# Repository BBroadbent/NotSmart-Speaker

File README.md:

# NotSmart Speaker

> **All the beats. None of the privacy risks.**

**NotSmart Speaker** is a custom, open-hardware local-first audio receiver designed to bring high-fidelity multi-room streaming to your home without the bloat, telemetry, or invasive microphones of commercial "smart" speakers. 

Powered by an ESP32 micro-controller, a PCM5100A I2S DAC, and a TPA3118 Class-D amplifier, it connects directly over Wi-Fi via the **Sendspin** protocol (integrating seamlessly with Home Assistant, Music Assistant, and local media setups).

---

## Features

- **100% Local & Cloud-Free:** No voice tracking, no external server dependency, no telemetry, and zero microphones.
- **20V USB-PD Powered:** Runs off a standard 45W+ USB-C laptop power brick using an onboard CH224K USB Power Delivery trigger IC.
- **Hi-Fi I2S Digital Path:** Uses the PCM5100A DAC to convert digital I2S audio signals straight from the ESP32.
- **Punchy Class-D Output:** Drives a single 4Ω mono speaker with up to ~40W cleanly via a TPA3118 amplifier in PBTL mode.
- **Clean Power Tree:** Dedicated buck step-down and low-noise LDO stages to protect sensitive audio lines from power noise.
- **Open Hardware:** Custom PCB layout engineered specifically for small desktop/shelf speaker enclosures.

---

## Hardware Architecture

### **Core Components**
| Component | Function |
| :--- | :--- |
| **ESP32** | Main microcontroller running local audio client firmware |
| **PCM5100A** | Dedicated I2S stereo/mono DAC |
| **TPA3118** | High-efficiency Class-D mono (PBTL) audio power amplifier |
| **CH224K** | Hardware USB-PD sink controller (Requests 20V profile) |
| **4Ω Mono Speaker** | Custom cabinet integration |

### **Power Architecture**

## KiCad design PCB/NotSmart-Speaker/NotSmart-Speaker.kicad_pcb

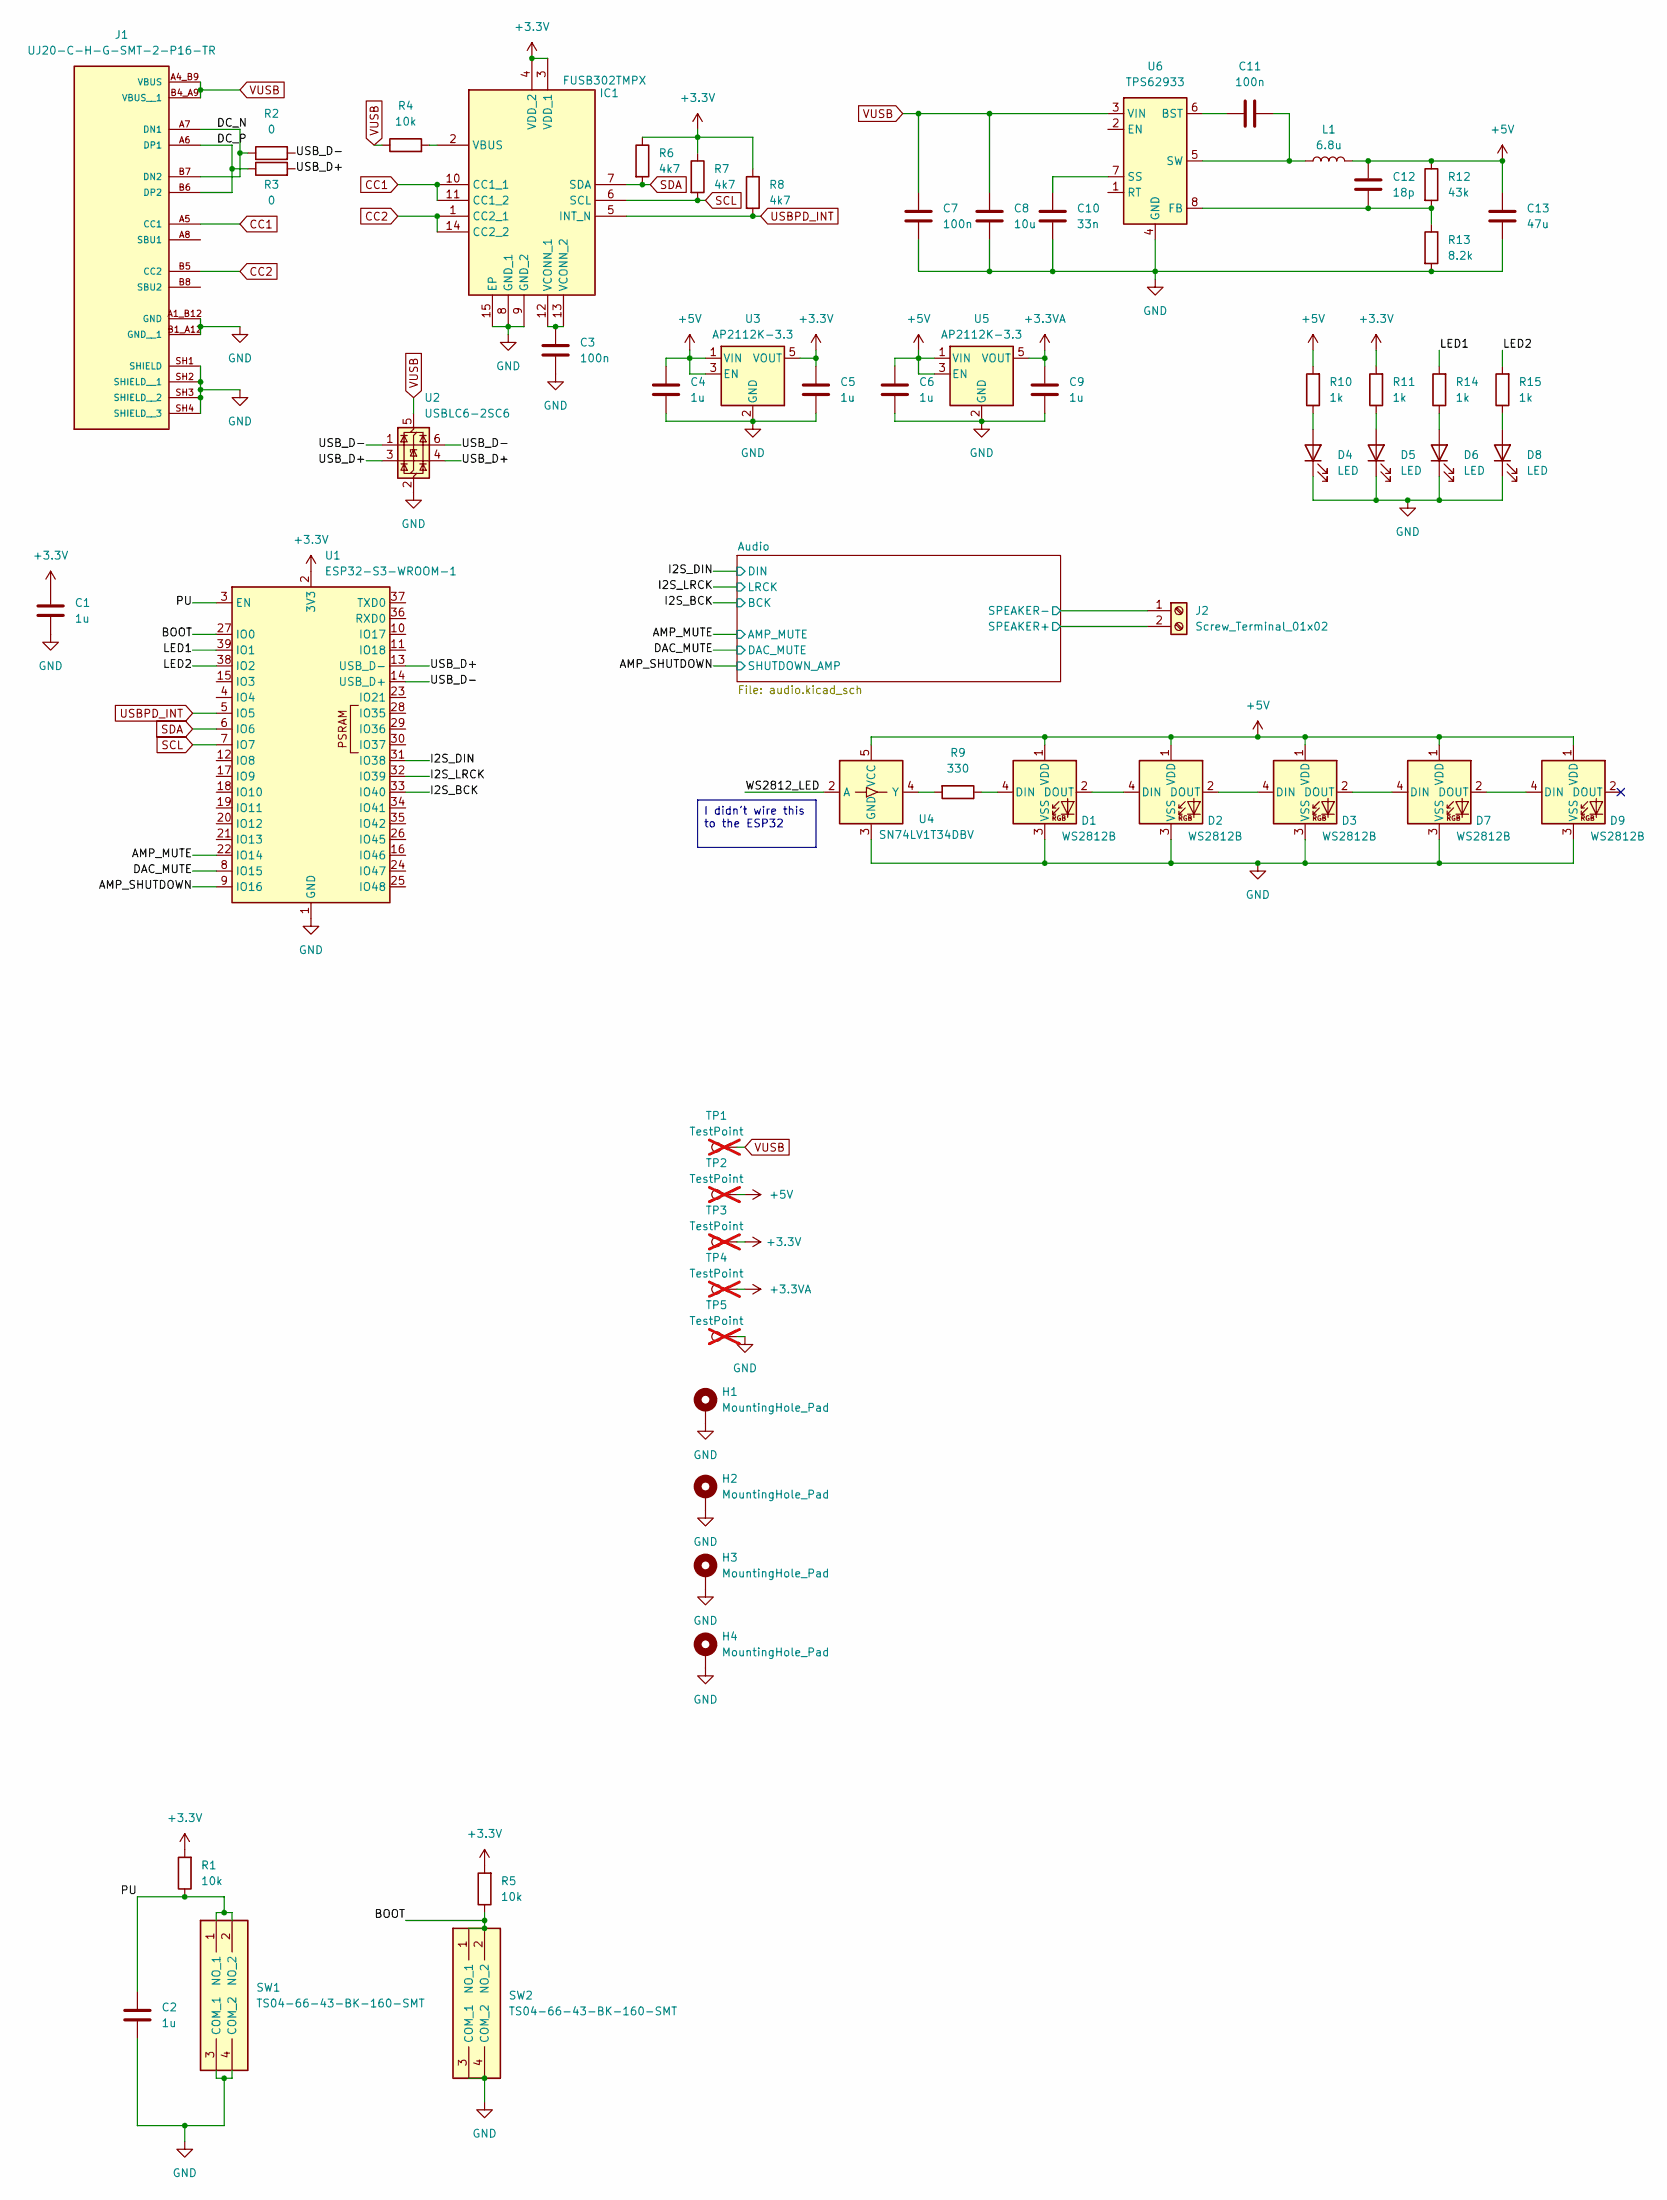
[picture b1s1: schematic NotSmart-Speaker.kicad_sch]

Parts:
C1, C2, C4, C5, C6, C9: 1u; C_0805_2012Metric_Pad1.18x1.45mm_HandSolder; Manufacturer_Part_Number GRM219R61H105MA73D
C3, C7, C11: 100n; C_0805_2012Metric_Pad1.18x1.45mm_HandSolder; Manufacturer_Part_Number 885012207098R
C8: 10u; C_0805_2012Metric_Pad1.18x1.45mm_HandSolder; Manufacturer_Part_Number GRM21BR61H106KE43K
C10: 33n; C_0805_2012Metric_Pad1.18x1.45mm_HandSolder; Manufacturer_Part_Number 885012207095
C12: 18p; C_0805_2012Metric_Pad1.18x1.45mm_HandSolder; Manufacturer_Part_Number 08055A180JAT4A
C13: 47u; C_0805_2012Metric_Pad1.18x1.45mm_HandSolder; Manufacturer_Part_Number MLASL21GBB5476MTNA01
D1, D2, D3, D7, D9: WS2812B; LED_WS2812B_PLCC4_5.0x5.0mm_P3.2mm
D4, D5: LED; LED_0805_2012Metric_Pad1.15x1.40mm_HandSolder; Manufacturer_Part_Number LTST-S220KGKT
D6: LED; LED_0805_2012Metric_Pad1.15x1.40mm_HandSolder; Manufacturer_Part_Number LTST-C171YKT
D8: LED; LED_0805_2012Metric_Pad1.15x1.40mm_HandSolder; Manufacturer_Part_Number 150080BS75000
H1, H2, H3, H4: MountingHole_Pad; MountingHole_3.2mm_M3_ISO14580_Pad_TopBottom
IC1: FUSB302TMPX; QFN50P250X250X80-15N; Mouser Part Number 512-FUSB302TMPX
J1: UJ20-C-H-G-SMT-2-P16-TR; SAMESKY_UJ20-C-H-G-SMT-2-P16-TR; PARTREV 1.0
J2: Screw_Terminal_01x02; TerminalBlock_Phoenix_PT-1,5-2-3.5-H_1x02_P3.50mm_Horizontal; Manufacturer_Part_Number 1751248
L1: 6.8u; WE-LHMI_7030_705048; Manufacturer_Part_Number 74437346068
R1, R4, R5: 10k; R_0805_2012Metric_Pad1.20x1.40mm_HandSolder; Manufacturer_Part_Number RC0805FR-0710KL
R2, R3: 0; R_0805_2012Metric_Pad1.20x1.40mm_HandSolder; Manufacturer_Part_Number CRCW08050000ZSTC
R6, R7, R8: 4k7; R_0805_2012Metric_Pad1.20x1.40mm_HandSolder; Manufacturer_Part_Number CR0805-FX-4701ELF
R9: 330; R_0805_2012Metric_Pad1.20x1.40mm_HandSolder; Manufacturer_Part_Number CRCW0805330RJNEA
R10, R11, R14, R15: 1k; R_0805_2012Metric_Pad1.20x1.40mm_HandSolder; Manufacturer_Part_Number AC0805FR-101KL
R12: 43k; R_0805_2012Metric_Pad1.20x1.40mm_HandSolder; Manufacturer_Part_Number ERJ-PB6B4302V
R13: 8.2k; R_0805_2012Metric_Pad1.20x1.40mm_HandSolder; Manufacturer_Part_Number ERJ-PB6B8201V
SW1, SW2: TS04-66-43-BK-160-SMT; TS046643BK160SMT; Mouser Part Number 179-TS046643BK160SMT
TP1, TP2, TP3, TP4, TP5: TestPoint; TestPoint_Pad_D1.5mm; not fitted
U1: ESP32-S3-WROOM-1; Manufacturer_Part_Number ESP32-S3-WROOM-1-N8R8
U2: USBLC6-2SC6; SOT-23-6; Manufacturer_Part_Number USBLC6-2SC6
U3, U5: AP2112K-3.3; SOT-23-5; Manufacturer_Part_Number 621-AP2112K-3.3TRG1
U4: SN74LV1T34DBV; SOT-23-5; Manufacturer_Part_Number SN74LV1T34DBVRG4
U6: TPS62933; SOT-583-8; Manufacturer_Part_Number TPS62933ODRLR

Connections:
+3.3V: C1.1, C5.1, IC1.3 (VDD_1), IC1.4 (VDD_2), R1.2, R5.2, R6.1, R7.1, R8.1, R11.2, TP3.1 (1_1), U1.2 (3V3), U3.5 (VOUT); also elsewhere on the board
+3.3VA: C9.1, TP4.1 (1_1), U5.5 (VOUT); also elsewhere on the board
+5V: C4.1, C6.1, C12.1, C13.1, D1.1 (VDD), D2.1 (VDD), D3.1 (VDD), D7.1 (VDD), D9.1 (VDD), L1.2, R10.2, R12.1, TP2.1 (1_1), U3.1 (VIN), U3.3 (EN), U4.5 (VCC), U5.1 (VIN), U5.3 (EN)
/AMP_MUTE: U1.22 (IO14); also elsewhere on the board
/AMP_SHUTDOWN: U1.9 (IO16); also elsewhere on the board
/Audio/SPEAKER+: J2.2; also elsewhere on the board
/Audio/SPEAKER-: J2.1; also elsewhere on the board
/BOOT: R5.1, SW2.1 (NO_1), SW2.2 (NO_2), U1.27 (IO0)
/DAC_MUTE: U1.8 (IO15); also elsewhere on the board
/DC_N: J1.A7 (DN1), J1.B7 (DN2), R2.1
/DC_P: J1.A6 (DP1), J1.B6 (DP2), R3.1
/I2S_BCK: U1.33 (IO40); also elsewhere on the board
/I2S_DIN: U1.31 (IO38); also elsewhere on the board
/I2S_LRCK: U1.32 (IO39); also elsewhere on the board
/LED1: R14.2, U1.39 (IO1)
/LED2: R15.2, U1.38 (IO2)
/PU: C2.1, R1.1, SW1.1 (NO_1), SW1.2 (NO_2), U1.3 (EN)
/USB_D+: R3.2, U1.13 (USB_D-), U2.3 (I/O2), U2.4 (I/O2)
/USB_D-: R2.2, U1.14 (USB_D+), U2.1 (I/O1), U2.6 (I/O1)
/WS2812_LED: U4.2 (A)
CC1: IC1.10 (CC1_1), IC1.11 (CC1_2), J1.A5 (CC1)
CC2: IC1.1 (CC2_1), IC1.14 (CC2_2), J1.B5 (CC2)
GND: C1.2, C2.2, C3.2, C4.2, C5.2, C6.2, C7.2, C8.2, C9.2, C10.2, C13.2, D1.3 (VSS), D2.3 (VSS), D3.3 (VSS), D4.1 (K), D5.1 (K), D6.1 (K), D7.3 (VSS), D8.1 (K), D9.3 (VSS), H1.1 (1_1), H2.1 (1_1), H3.1 (1_1), H4.1 (1_1), IC1.8 (GND_1), IC1.9 (GND_2), IC1.15 (EP), J1.A1_B12 (GND), J1.B1_A12 (GND__1), J1.SH1 (SHIELD), J1.SH2 (SHIELD__1), J1.SH3 (SHIELD__2), J1.SH4 (SHIELD__3), R13.2, SW1.3 (COM_1), SW1.4 (COM_2), SW2.3 (COM_1), SW2.4 (COM_2), TP5.1 (1_1), U1.1 (GND), U1.40 (GND), U1.41 (GND), U2.2 (GND), U3.2 (GND), U4.3 (GND), U5.2 (GND), U6.4 (GND); also elsewhere on the board
unnamed: D1.4 (DIN), R9.1
unnamed: D1.2 (DOUT), D2.4 (DIN)
unnamed: D2.2 (DOUT), D3.4 (DIN)
unnamed: D3.2 (DOUT), D7.4 (DIN)
unnamed: D4.2 (A), R10.1
unnamed: D5.2 (A), R11.1
unnamed: D6.2 (A), R14.1
unnamed: D7.2 (DOUT), D9.4 (DIN)
unnamed: D8.2 (A), R15.1
unnamed: IC1.2 (VBUS), R4.2
unnamed: C3.1, IC1.12 (VCONN_1), IC1.13 (VCONN_2)
unnamed: R9.2, U4.4 (Y)
unnamed: C11.1, U6.6 (BST)
unnamed: C12.2, R12.2, R13.1, U6.8 (FB)
unnamed: C10.1, U6.7 (SS)
unnamed: C11.2, L1.1, U6.5 (SW)
SCL: IC1.6 (SCL), R7.2, U1.7 (IO7)
SDA: IC1.7 (SDA), R6.2, U1.6 (IO6)
USBPD_INT: IC1.5 (INT_N), R8.2, U1.5 (IO5)
VUSB: C7.1, C8.1, J1.A4_B9 (VBUS), J1.B4_A9 (VBUS__1), R4.1, TP1.1 (1_1), U2.5 (VBUS), U6.3 (VIN); also elsewhere on the board

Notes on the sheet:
I didn't wire this to the ESP32

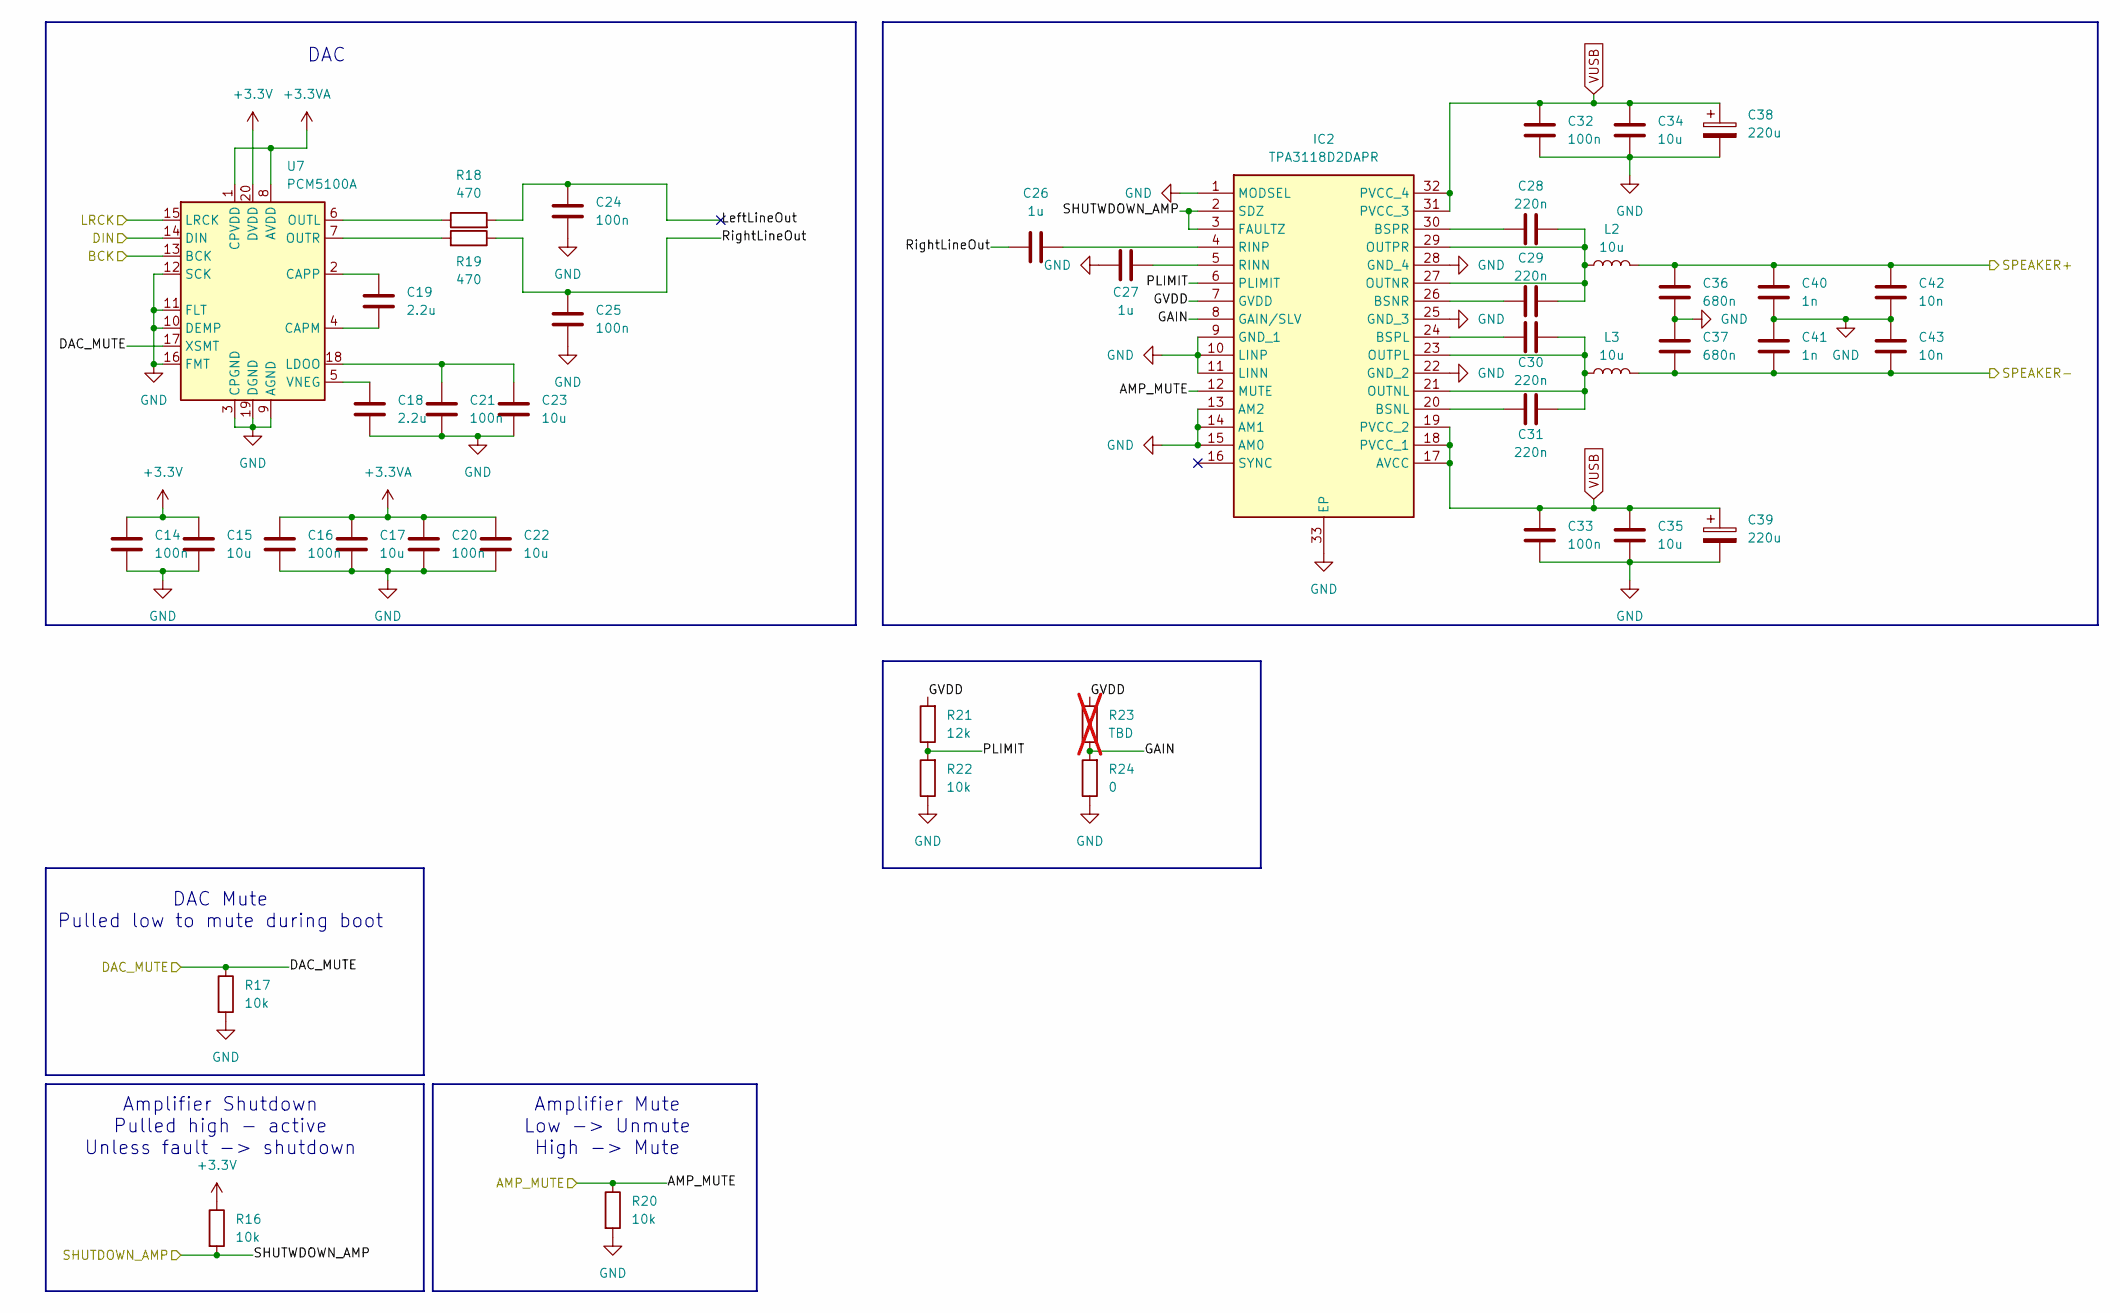
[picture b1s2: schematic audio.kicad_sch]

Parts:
C14, C16, C20, C21, C24, C25, C32, C33: 100n; C_0805_2012Metric_Pad1.18x1.45mm_HandSolder; Manufacturer_Part_Number 885012207098R
C15, C17, C22, C23: 10u; C_0805_2012Metric_Pad1.18x1.45mm_HandSolder; Manufacturer_Part_Number GRM21BR61H106KE43K
C18, C19: 2.2u; C_0805_2012Metric_Pad1.18x1.45mm_HandSolder; Manufacturer_Part_Number CL21B225KAFNNNE
C26, C27: 1u; C_0805_2012Metric_Pad1.18x1.45mm_HandSolder; Manufacturer_Part_Number GRM219R61H105MA73D
C28, C29, C30, C31: 220n; C_0805_2012Metric_Pad1.18x1.45mm_HandSolder; Manufacturer_Part_Number CL21B225KBYNNWE
C34, C35: 10u; C_1206_3216Metric_Pad1.33x1.80mm_HandSolder; Manufacturer_Part_Number GRM31CR71E106MA12L
C36, C37: 680n; C_1206_3216Metric_Pad1.33x1.80mm_HandSolder; Manufacturer_Part_Number 885012208092
C38, C39: 220u; CP_Elec_10x10; Manufacturer_Part_Number EEH-ZS1H221P
C40, C41: 1n; C_0805_2012Metric_Pad1.18x1.45mm_HandSolder; Manufacturer_Part_Number 885012207086
C42, C43: 10n; C_0805_2012Metric_Pad1.18x1.45mm_HandSolder; Manufacturer_Part_Number 08055C103KAT2A
IC2: TPA3118D2DAPR; SOP65P810X120-33N; Mouser Part Number 595-TPA3118D2DAPR
L2, L3: 10u; WE-LHMI_7030_705048; Manufacturer_Part_Number 74437346100
R16, R17, R20, R22: 10k; R_0805_2012Metric_Pad1.20x1.40mm_HandSolder; Manufacturer_Part_Number RC0805FR-0710KL
R18, R19: 470; R_0805_2012Metric_Pad1.20x1.40mm_HandSolder; Manufacturer_Part_Number CR0805-JW-471ELF
R21: 12k; R_0805_2012Metric_Pad1.20x1.40mm_HandSolder; Manufacturer_Part_Number CRCW080512K0JNEA
R23: TBD; R_0805_2012Metric_Pad1.20x1.40mm_HandSolder; not fitted
R24: 0; R_0805_2012Metric_Pad1.20x1.40mm_HandSolder; Manufacturer_Part_Number CRCW08050000ZSTC
U7: PCM5100A; TSSOP-20_4.4x6.5mm_P0.65mm; Manufacturer_Part_Number PCM5100APWR

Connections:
+3.3V: C14.1, C15.1, R16.1, U7.20 (DVDD); also elsewhere on the board
+3.3VA: C16.1, C17.1, C20.1, C22.1, U7.1 (CPVDD), U7.8 (AVDD); also elsewhere on the board
/AMP_MUTE: IC2.12 (MUTE), R20.1; also elsewhere on the board
/AMP_SHUTDOWN: IC2.2 (SDZ), IC2.3 (FAULTZ), R16.2; also elsewhere on the board
/Audio/GAIN: IC2.8 (GAIN/SLV), R23.1, R24.2
/Audio/GVDD: IC2.7 (GVDD), R21.2, R23.2
/Audio/LeftLineOut: C24.1, R18.2
/Audio/PLIMIT: IC2.6 (PLIMIT), R21.1, R22.2
/Audio/RightLineOut: C25.1, C26.1, R19.1
/Audio/SPEAKER+: C36.1, C40.1, C42.1, L2.2; also elsewhere on the board
/Audio/SPEAKER-: C37.2, C41.2, C43.2, L3.2; also elsewhere on the board
/DAC_MUTE: R17.1, U7.17 (XSMT); also elsewhere on the board
/I2S_BCK: U7.13 (BCK); also elsewhere on the board
/I2S_DIN: U7.14 (DIN); also elsewhere on the board
/I2S_LRCK: U7.15 (LRCK); also elsewhere on the board
GND: C14.2, C15.2, C16.2, C17.2, C18.2, C20.2, C21.2, C22.2, C23.2, C24.2, C25.2, C27.1, C32.2, C33.2, C34.2, C35.2, C36.2, C37.1, C38.2, C39.2, C40.2, C41.1, C42.2, C43.1, IC2.1 (MODSEL), IC2.9 (GND_1), IC2.10 (LINP), IC2.11 (LINN), IC2.13 (AM2), IC2.14 (AM1), IC2.15 (AM0), IC2.22 (GND_2), IC2.25 (GND_3), IC2.28 (GND_4), IC2.33 (EP), R17.2, R20.2, R22.1, R24.1, U7.3 (CPGND), U7.9 (AGND), U7.10 (DEMP), U7.11 (FLT), U7.12 (SCK), U7.16 (FMT), U7.19 (DGND); also elsewhere on the board
unnamed: C31.1, IC2.20 (BSNL)
unnamed: C29.1, IC2.26 (BSNR)
unnamed: C30.1, IC2.24 (BSPL)
unnamed: C28.1, IC2.30 (BSPR)
unnamed: C30.2, C31.2, IC2.21 (OUTNL), IC2.23 (OUTPL), L3.1
unnamed: C28.2, C29.2, IC2.27 (OUTNR), IC2.29 (OUTPR), L2.1
unnamed: C27.2, IC2.5 (RINN)
unnamed: C26.2, IC2.4 (RINP)
unnamed: C19.2, U7.4 (CAPM)
unnamed: C19.1, U7.2 (CAPP)
unnamed: C21.1, C23.1, U7.18 (LDOO)
unnamed: R18.1, U7.6 (OUTL)
unnamed: R19.2, U7.7 (OUTR)
unnamed: C18.1, U7.5 (VNEG)
VUSB: C32.1, C33.1, C34.1, C35.1, C38.1, C39.1, IC2.17 (AVCC), IC2.18 (PVCC_1), IC2.19 (PVCC_2), IC2.31 (PVCC_3), IC2.32 (PVCC_4); also elsewhere on the board

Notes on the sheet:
DAC
Amplifier Shutdown Pulled high - active Unless fault -> shutdown
DAC Mute Pulled low to mute during boot
Amplifier Mute Low -> Unmute High -> Mute

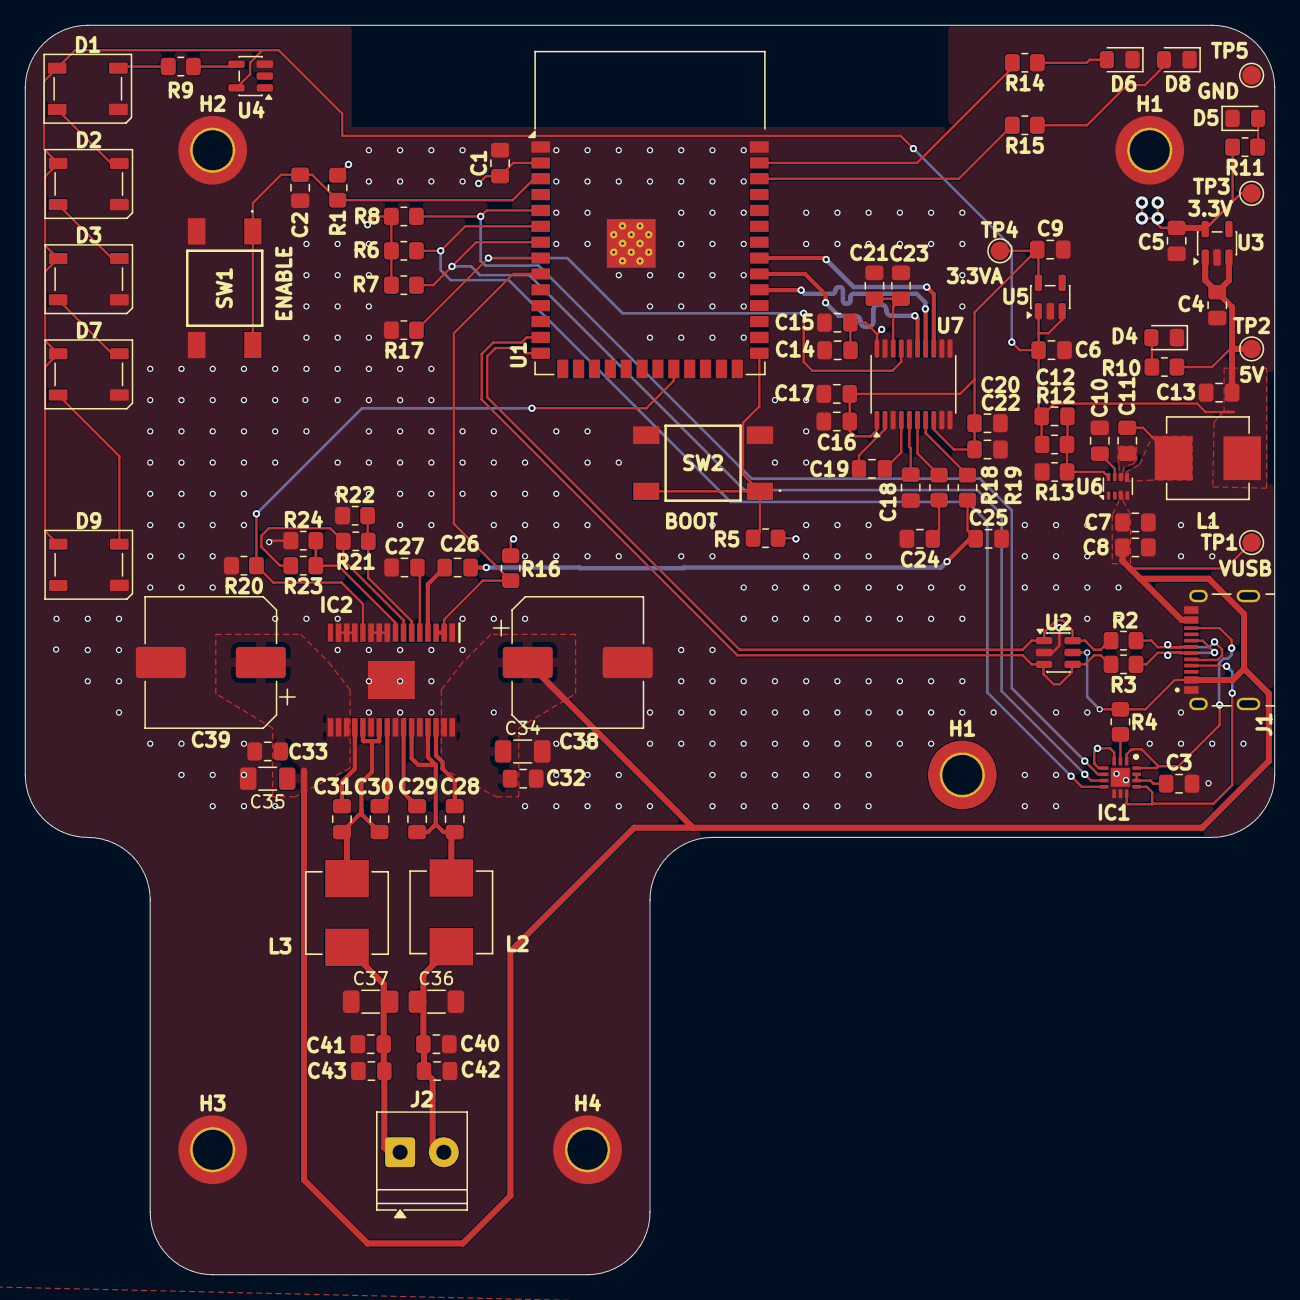
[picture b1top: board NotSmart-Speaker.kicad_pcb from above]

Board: 4 copper layers, 100.0 x 100.0 mm, 102 parts (0 on the bottom side), 61 nets.

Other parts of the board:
H1#2: MountingHole_Pad; MountingHole_3.2mm_M3_ISO14580_Pad_TopBottom
